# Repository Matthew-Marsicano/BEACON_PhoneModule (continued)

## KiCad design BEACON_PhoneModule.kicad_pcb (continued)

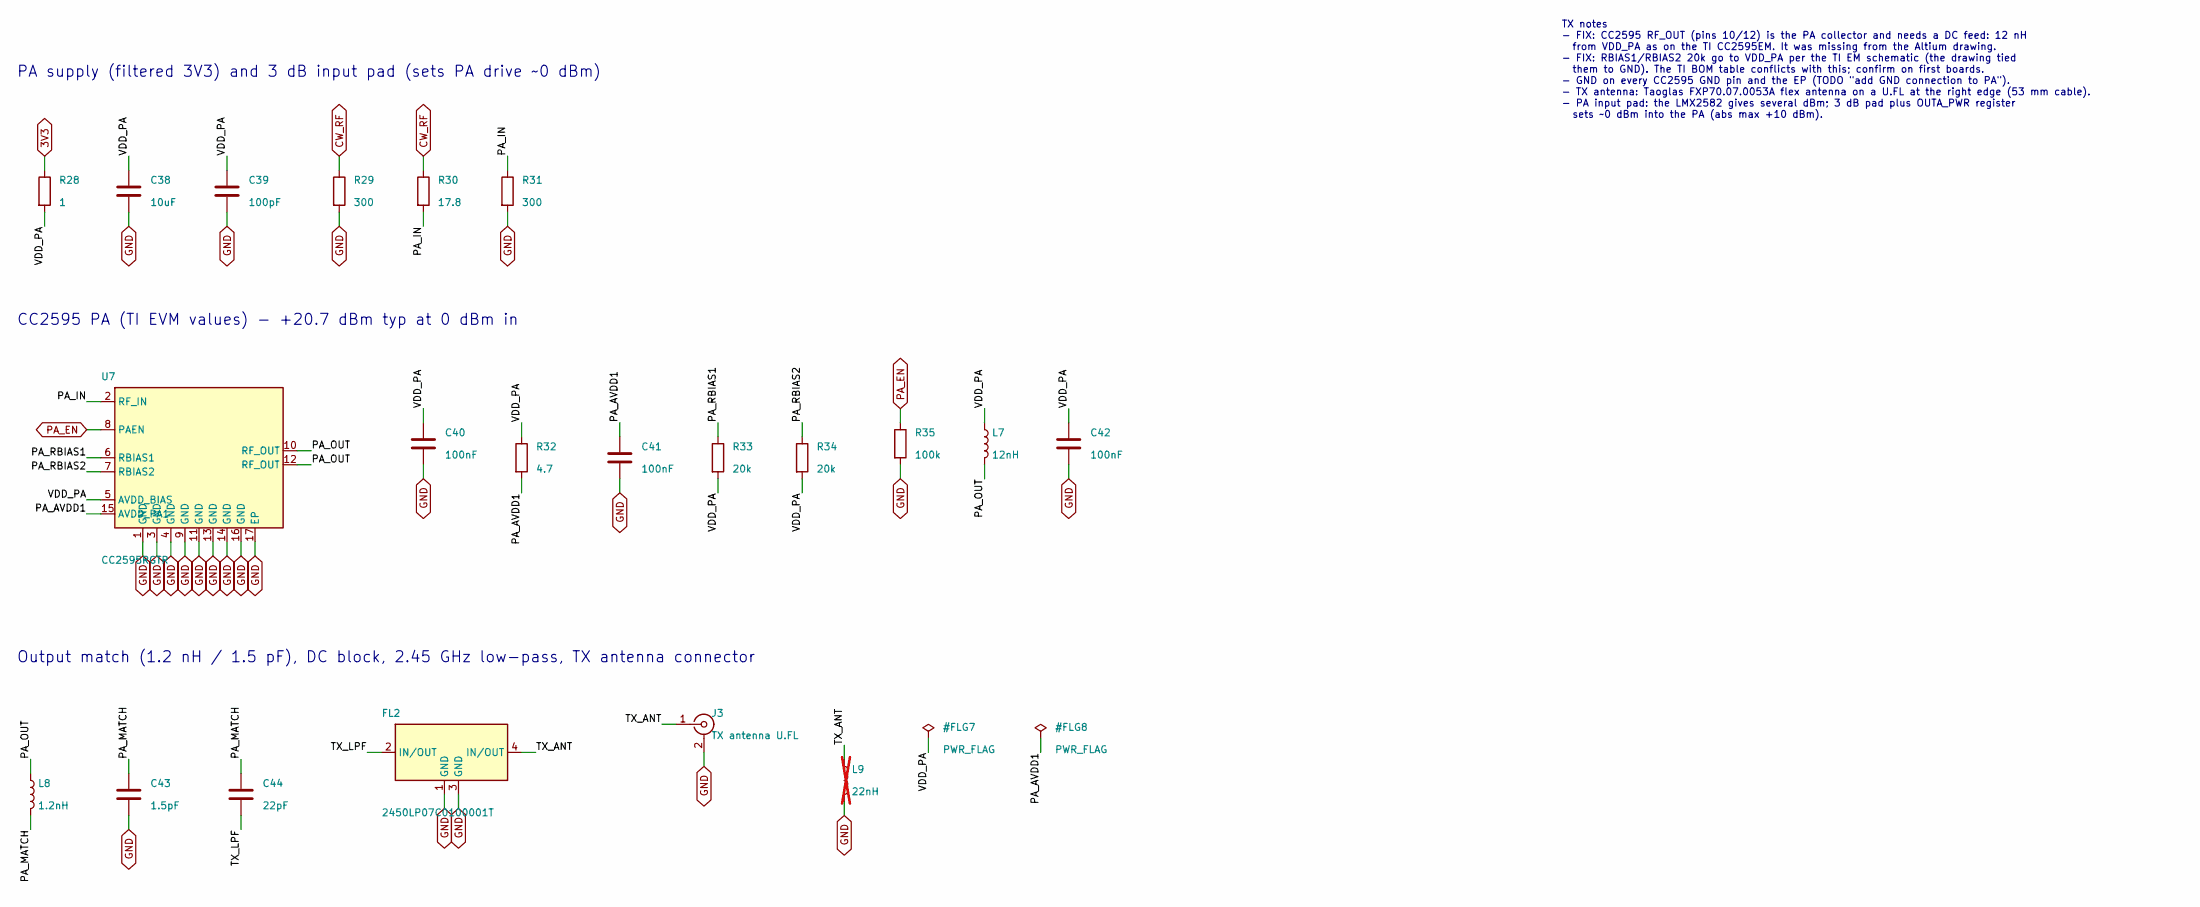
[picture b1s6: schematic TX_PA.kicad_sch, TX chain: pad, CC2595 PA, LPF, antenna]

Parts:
C38: 10uF; C38_C_0603_1608Metric
C39: 100pF; C39_C_0402_1005Metric
C40: 100nF; C40_C_0402_1005Metric
C41: 100nF; C41_C_0402_1005Metric
C42: 100nF; C42_C_0402_1005Metric
C43: 1.5pF; C43_C_0402_1005Metric; MPN 0402CG1R5C500NT
C44: 22pF; C44_C_0402_1005Metric
FL2: 2450LP07C0100001T; FL2_Johanson_2450LP07_0402_4T; MPN 2450LP07C0100001T
J3: TX antenna U.FL; J3_U.FL_Hirose_U.FL-R-SMT-1_Vertical; MPN U.FL-R-SMT-1(10)
L7: 12nH; L7_L_0402_1005Metric; MPN LQW15AN12NG00D; LCSC C86128
L8: 1.2nH; L8_L_0402_1005Metric; MPN LQG15HS1N2B02D; LCSC C488336
L9: 22nH; L9_L_0402_1005Metric; MPN LQW15AN22NJ00D; not fitted
R28: 1; R28_R_0603_1608Metric
R29: 300; R29_R_0402_1005Metric
R30: 17.8; R30_R_0402_1005Metric
R31: 300; R31_R_0402_1005Metric
R32: 4.7; R32_R_0402_1005Metric
R33: 20k; R33_R_0402_1005Metric
R34: 20k; R34_R_0402_1005Metric
R35: 100k; R35_R_0402_1005Metric
U7: CC2595RGTR; U7_VQFN-16-1EP_3x3mm_P0.5mm_EP1.68x1.68mm_ThermalVias; MPN CC2595RGTR

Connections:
3V3: R28.1; also elsewhere on the board
/TX_PA/PA_AVDD1: C41.1, R32.2, U7.15 (AVDD_PA1)
/TX_PA/PA_IN: R30.2, R31.1, U7.2 (RF_IN)
/TX_PA/PA_MATCH: C43.1, C44.1, L8.2
/TX_PA/PA_OUT: L7.2, L8.1, U7.10 (RF_OUT), U7.12 (RF_OUT)
/TX_PA/PA_RBIAS1: R33.1, U7.6 (RBIAS1)
/TX_PA/PA_RBIAS2: R34.1, U7.7 (RBIAS2)
/TX_PA/TX_ANT: FL2.4 (IN/OUT), J3.1 (In), L9.1
/TX_PA/TX_LPF: C44.2, FL2.2 (IN/OUT)
/TX_PA/VDD_PA: C38.1, C39.1, C40.1, C42.1, L7.1, R28.2, R32.1, R33.2, R34.2, U7.5 (AVDD_BIAS)
CW_RF: R29.1, R30.1; also elsewhere on the board
GND: C38.2, C39.2, C40.2, C41.2, C42.2, C43.2, FL2.1 (GND), FL2.3 (GND), J3.2 (Ext), L9.2, R29.2, R31.2, R35.2, U7.1 (GND), U7.3 (GND), U7.4 (GND), U7.9 (GND), U7.11 (GND), U7.13 (GND), U7.14 (GND), U7.16 (GND), U7.17 (EP); also elsewhere on the board
PA_EN: R35.1, U7.8 (PAEN); also elsewhere on the board

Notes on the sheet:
PA supply (filtered 3V3) and 3 dB input pad (sets PA drive ~0 dBm)
CC2595 PA (TI EVM values) - +20.7 dBm typ at 0 dBm in
Output match (1.2 nH / 1.5 pF), DC block, 2.45 GHz low-pass, TX antenna connector
TX notes - FIX: CC2595 RF_OUT (pins 10/12) is the PA collector and needs a DC feed: 12 nH from VDD_PA as on the TI CC2595EM. It was missing from the Altium drawing. - FIX: RBIAS1/RBIAS2 20k go to VDD_PA per the TI EM schematic (the drawing tied them to GND). The TI BOM table conflicts with this; co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

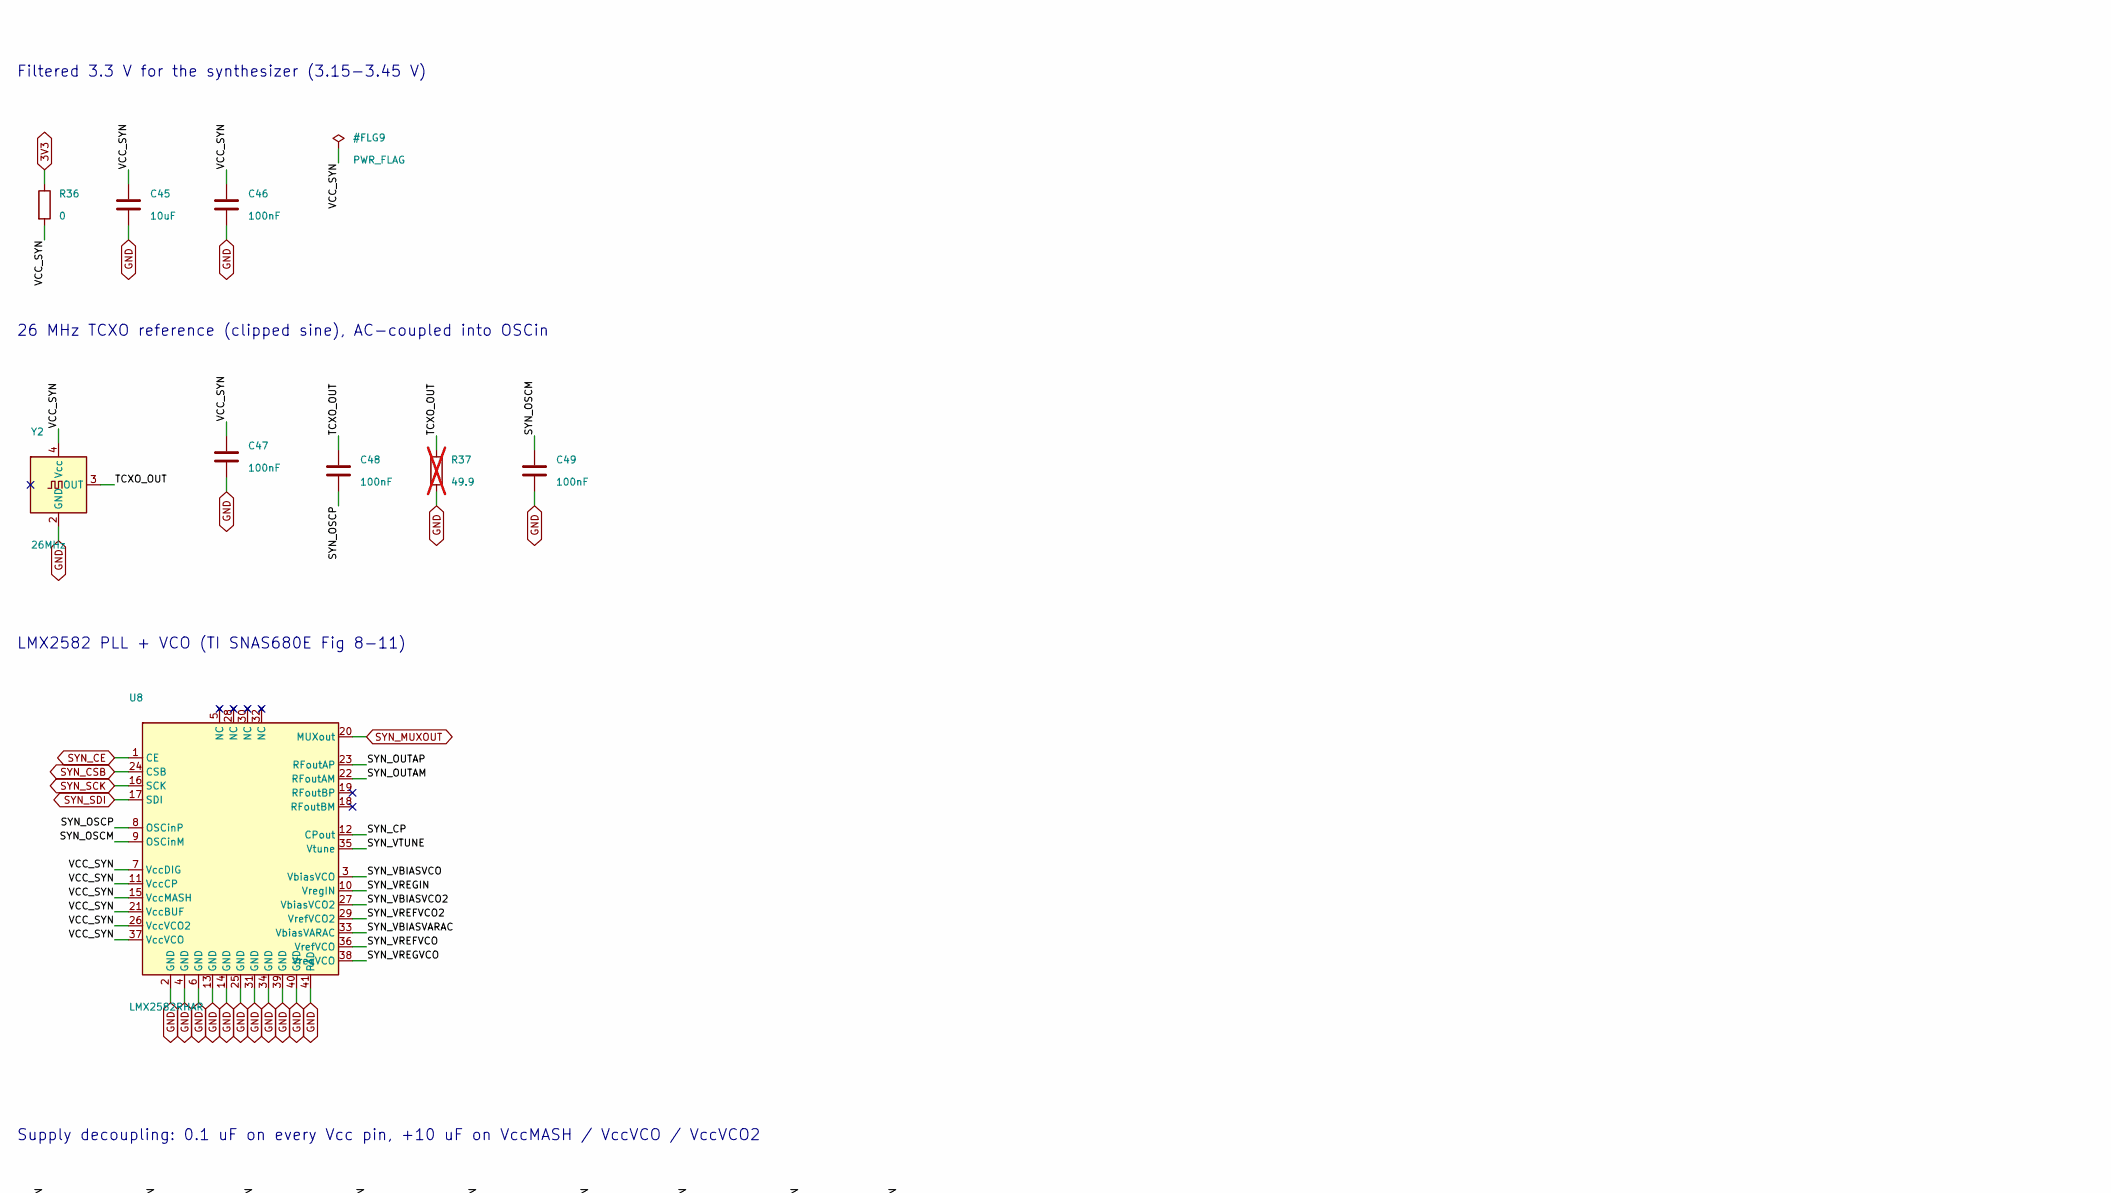
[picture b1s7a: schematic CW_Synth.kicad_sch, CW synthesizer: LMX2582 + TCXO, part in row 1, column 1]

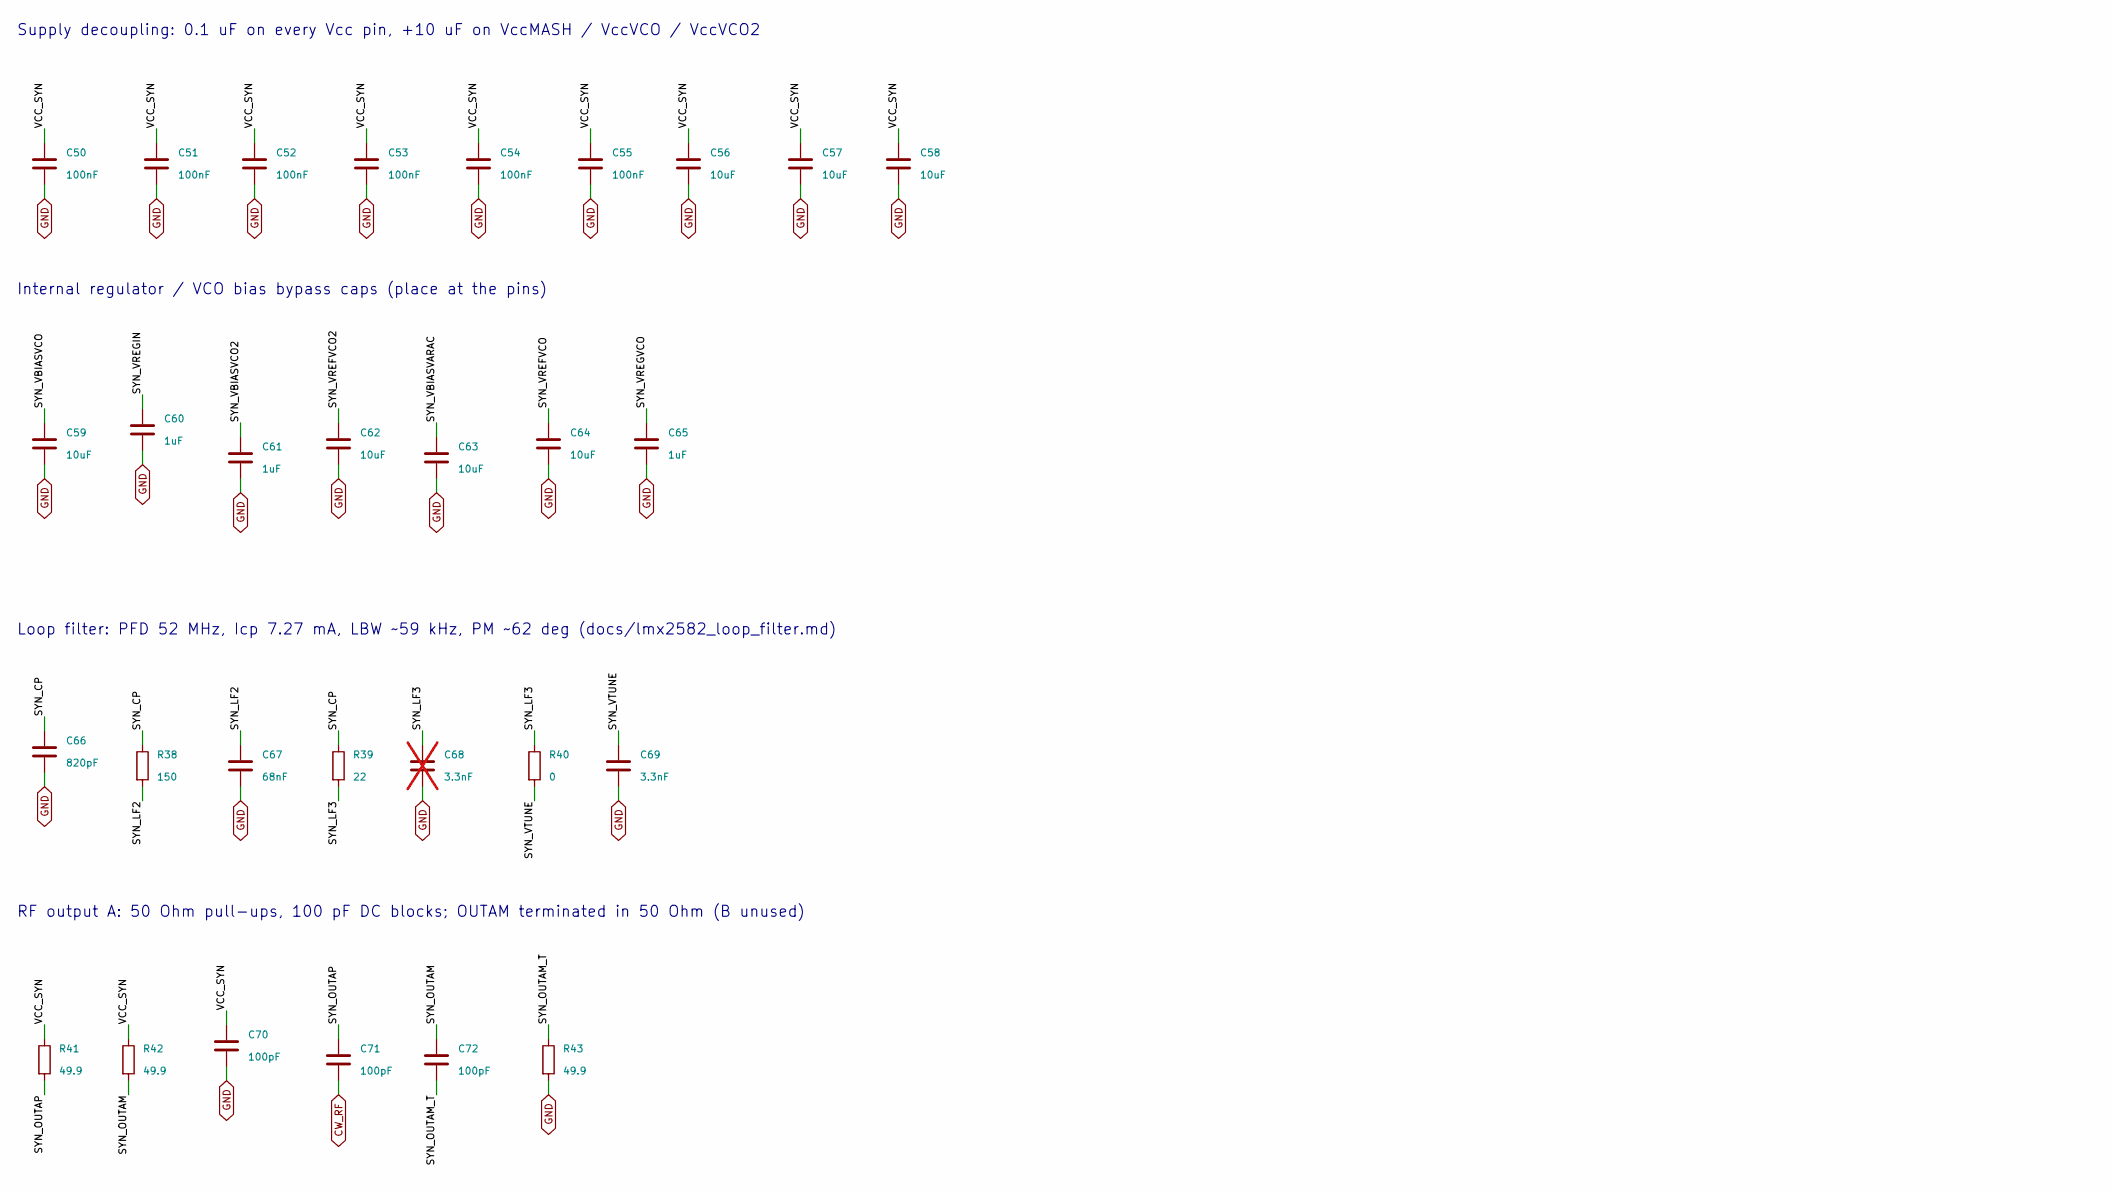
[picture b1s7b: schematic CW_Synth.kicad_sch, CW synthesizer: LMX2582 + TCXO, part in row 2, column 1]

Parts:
C45: 10uF; C45_C_0603_1608Metric
C46: 100nF; C46_C_0402_1005Metric
C47: 100nF; C47_C_0402_1005Metric
C48: 100nF; C48_C_0402_1005Metric
C49: 100nF; C49_C_0402_1005Metric
C50: 100nF; C50_C_0402_1005Metric
C51: 100nF; C51_C_0402_1005Metric
C52: 100nF; C52_C_0402_1005Metric
C53: 100nF; C53_C_0402_1005Metric
C54: 100nF; C54_C_0402_1005Metric
C55: 100nF; C55_C_0402_1005Metric
C56: 10uF; C56_C_0603_1608Metric
C57: 10uF; C57_C_0603_1608Metric
C58: 10uF; C58_C_0603_1608Metric
C59: 10uF; C59_C_0603_1608Metric
C60: 1uF; C60_C_0402_1005Metric
C61: 1uF; C61_C_0402_1005Metric
C62: 10uF; C62_C_0603_1608Metric
C63: 10uF; C63_C_0603_1608Metric
C64: 10uF; C64_C_0603_1608Metric
C65: 1uF; C65_C_0402_1005Metric
C66: 820pF; C66_C_0402_1005Metric
C67: 68nF; C67_C_0603_1608Metric; MPN CL10B683KB8NNNC; LCSC C31658
C68: 3.3nF; C68_C_0402_1005Metric; not fitted
C69: 3.3nF; C69_C_0402_1005Metric
C70: 100pF; C70_C_0402_1005Metric
C71: 100pF; C71_C_0402_1005Metric
C72: 100pF; C72_C_0402_1005Metric
R36: 0; R36_R_0603_1608Metric
R37: 49.9; R37_R_0402_1005Metric; not fitted
R38: 150; R38_R_0402_1005Metric
R39: 22; R39_R_0402_1005Metric
R40: 0; R40_R_0402_1005Metric
R41: 49.9; R41_R_0402_1005Metric
R42: 49.9; R42_R_0402_1005Metric
R43: 49.9; R43_R_0402_1005Metric
U8: LMX2582RHAR; U8_Texas_RHA_VQFN-40-1EP_6x6mm_P0.5mm_EP4.6x4.6mm_ThermalVi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; MPN LMX2582RHAR
Y2: 26MHz; Y2_Oscillator_SMD_SeikoEpson_TG2520SMN-xxx-xxxxxx-4Pin_2.5x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; MPN X1G0054210204; LCSC C7527389

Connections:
3V3: R36.1; also elsewhere on the board
/CW_Synth/SYN_CP: C66.1, R38.1, R39.1, U8.12 (CPout)
/CW_Synth/SYN_LF2: C67.1, R38.2
/CW_Synth/SYN_LF3: C68.1, R39.2, R40.1
/CW_Synth/SYN_OSCM: C49.1, U8.9 (OSCinM)
/CW_Synth/SYN_OSCP: C48.2, U8.8 (OSCinP)
/CW_Synth/SYN_OUTAM: C72.1, R42.2, U8.22 (RFoutAM)
/CW_Synth/SYN_OUTAM_T: C72.2, R43.1
/CW_Synth/SYN_OUTAP: C71.1, R41.2, U8.23 (RFoutAP)
/CW_Synth/SYN_VBIASVARAC: C63.1, U8.33 (VbiasVARAC)
/CW_Synth/SYN_VBIASVCO: C59.1, U8.3 (VbiasVCO)
/CW_Synth/SYN_VBIASVCO2: C61.1, U8.27 (VbiasVCO2)
/CW_Synth/SYN_VREFVCO: C64.1, U8.36 (VrefVCO)
/CW_Synth/SYN_VREFVCO2: C62.1, U8.29 (VrefVCO2)
/CW_Synth/SYN_VREGIN: C60.1, U8.10 (VregIN)
/CW_Synth/SYN_VREGVCO: C65.1, U8.38 (VregVCO)
/CW_Synth/SYN_VTUNE: C69.1, R40.2, U8.35 (Vtune)
/CW_Synth/TCXO_OUT: C48.1, R37.1, Y2.3 (OUT)
/CW_Synth/VCC_SYN: C45.1, C46.1, C47.1, C50.1, C51.1, C52.1, C53.1, C54.1, C55.1, C56.1, C57.1, C58.1, C70.1, R36.2, R41.1, R42.1, U8.7 (VccDIG), U8.11 (VccCP), U8.15 (VccMASH), U8.21 (VccBUF), U8.26 (VccVCO2), U8.37 (VccVCO), Y2.4 (Vcc)
CW_RF: C71.2; also elsewhere on the board
GND: C45.2, C46.2, C47.2, C49.2, C50.2, C51.2, C52.2, C53.2, C54.2, C55.2, C56.2, C57.2, C58.2, C59.2, C60.2, C61.2, C62.2, C63.2, C64.2, C65.2, C66.2, C67.2, C68.2, C69.2, C70.2, R37.2, R43.2, U8.2 (GND), U8.4 (GND), U8.6 (GND), U8.13 (GND), U8.14 (GND), U8.25 (GND), U8.31 (GND), U8.34 (GND), U8.39 (GND), U8.40 (GND), U8.41 (PAD), Y2.2 (GND); also elsewhere on the board
SYN_CE: U8.1 (CE); also elsewhere on the board
SYN_CSB: U8.24 (CSB); also elsewhere on the board
SYN_MUXOUT: U8.20 (MUXout); also elsewhere on the board
SYN_SCK: U8.16 (SCK); also elsewhere on the board
SYN_SDI: U8.17 (SDI); also elsewhere on the board

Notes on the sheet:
Filtered 3.3 V for the synthesizer (3.15-3.45 V)
26 MHz TCXO reference (clipped sine), AC-coupled into OSCin
LMX2582 PLL + VCO (TI SNAS680E Fig 8-11)
Supply decoupling: 0.1 uF on every Vcc pin, +10 uF on VccMASH / VccVCO / VccVCO2
Internal regulator / VCO bias bypass caps (place at the pins)
Loop filter: PFD 52 MHz, Icp 7.27 mA, LBW ~59 kHz, PM ~62 deg (docs/lmx2582_loop_filter.md)
RF output A: 50 Ohm pull-ups, 100 pF DC blocks; OUTAM terminated in 50 Ohm (B unused)
CW synthesizer notes (completed from the TI typical application) - Carrier: 2400-2483.5 MHz ISM. VCO 3.55-7.1 GHz, CHDIV=2 -> 2.4 GHz on OUTA. - Reference: 26 MHz TCXO. The PFD can use the OSCin doubler (52 MHz) in fractional mode. - SPI: SCK/SDI/CSB from the nRF52840; MUXout = lock detect or SPI r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

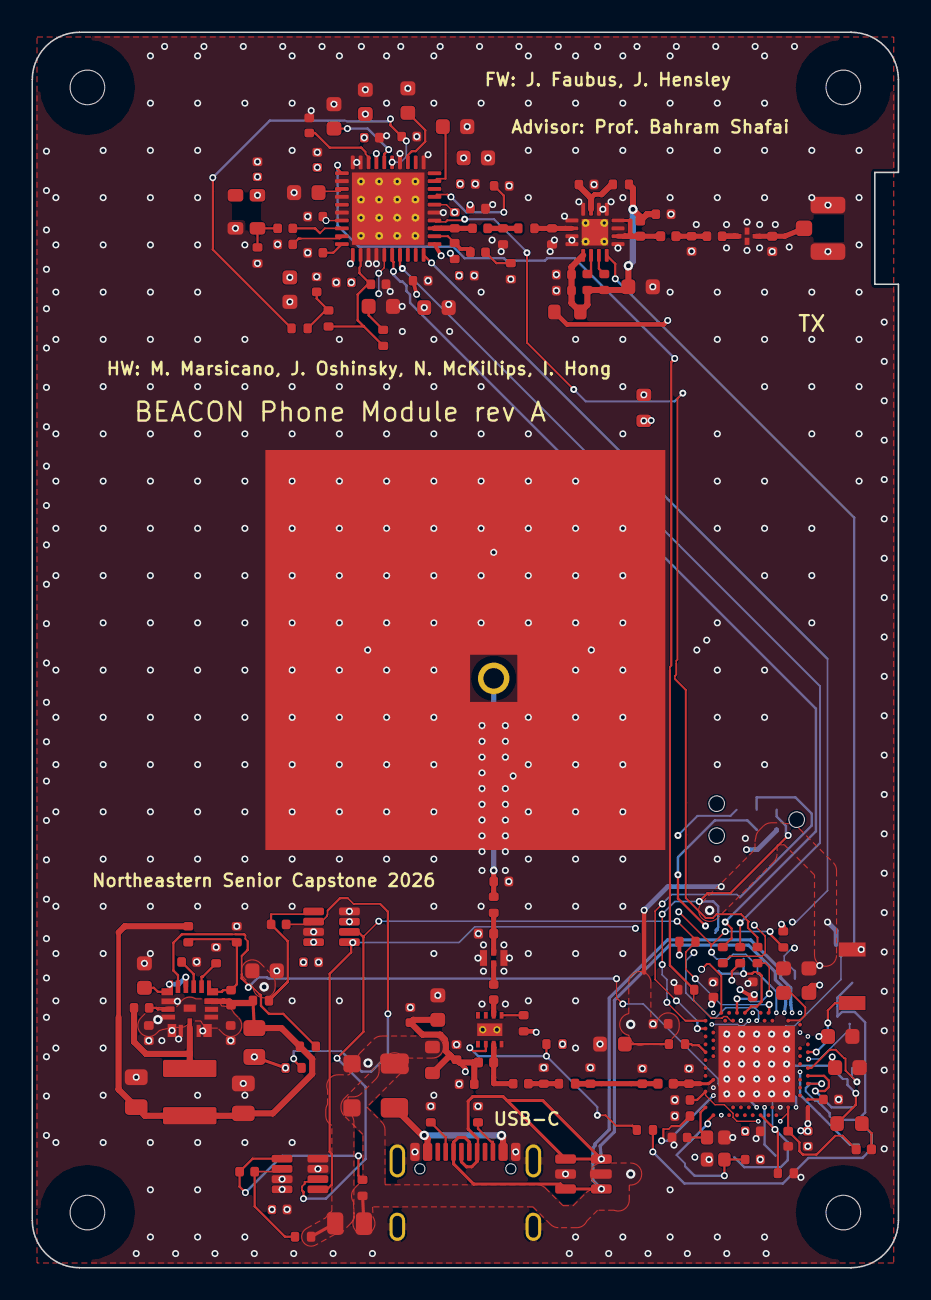
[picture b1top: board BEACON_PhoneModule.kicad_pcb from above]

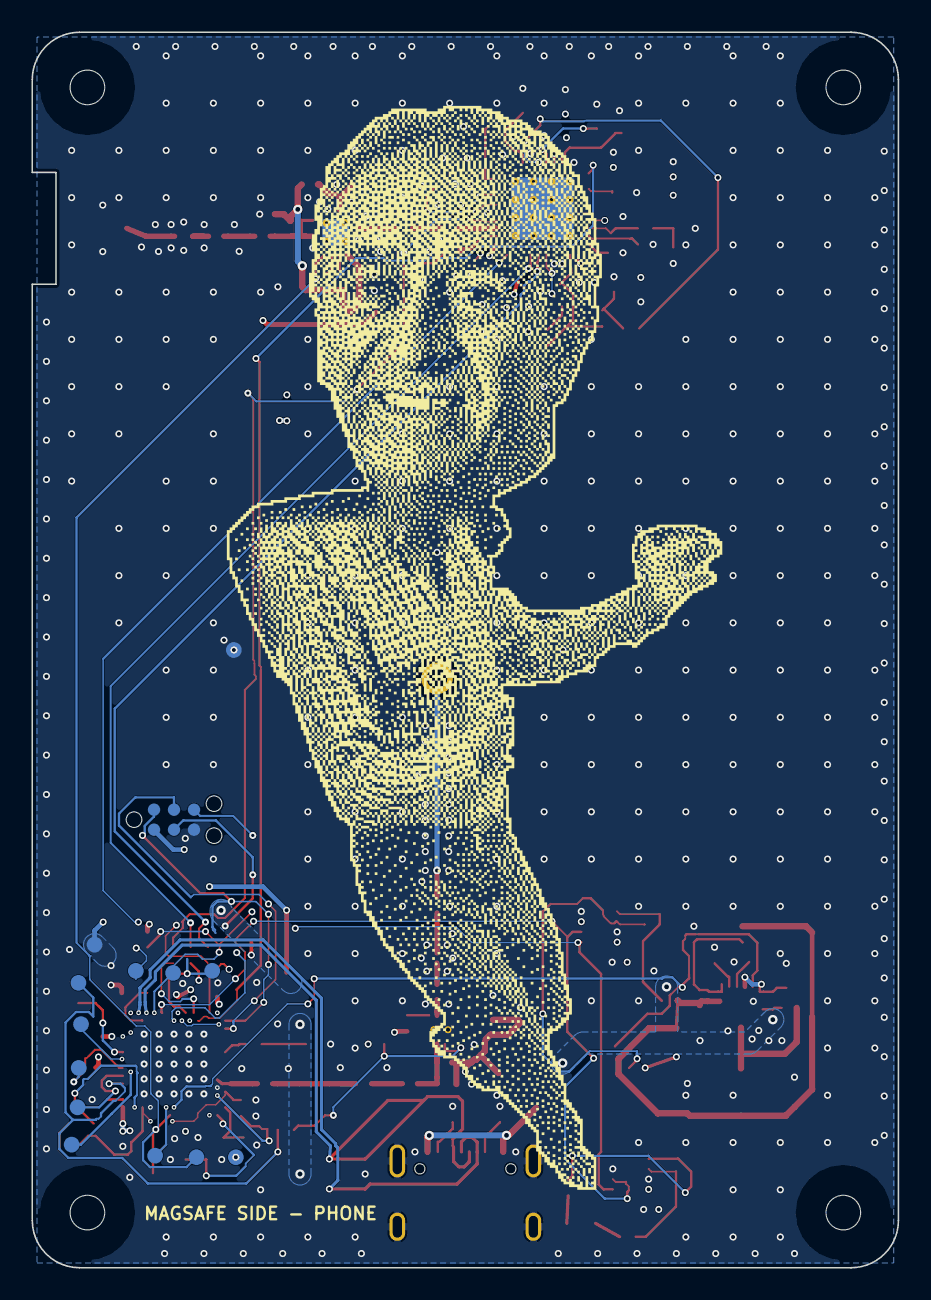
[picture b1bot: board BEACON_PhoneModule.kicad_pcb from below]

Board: 4 copper layers, 55.0 x 78.4 mm, 161 parts (14 on the bottom side), 92 nets.

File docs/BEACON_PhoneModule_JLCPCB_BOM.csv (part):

Comment,Designator,Footprint,LCSC Part #,MPN,Manufacturer,Quantity,Type,Notes
1uF,"C1,C16,C25,C35,C60,C61,C65",C_0402_1005Metric,C52923,CL05A105KA5NQNC,Samsung Electro-Mechanics,7,Basic,"1uF 25V X5R 10%. 25 V covers the 5V_BUS/5V0/LNA_VCC caps (C1, C35)."
100nF,"C2,C3,C4,C5,C7,C8,C11,C17,C18,C19,C23,C40,C41,C42,C46,C47,C48,C49,C50,C51,C52,C53,C54,C55",C_0402_1005Metric,C1525,CL05B104KO5NNNC,Samsung Electro-Mechanics,24,Basic,"100nF 16V X7R 10%. 16 V covers the 5V0 hot-loop caps (C7, C8)."
4.7uF,"C6,C15,C20,C21,C22",C_0603_1608Metric,C19666,CL10A475KO8NNNC,Samsung Electro-Mechanics,5,Basic,4.7uF 16V X5R 10%. 16 V covers 5V0 (C6) and VBUS (C21).
22nF,C9,C_0402_1005Metric,C1532,0402B223K500NT,FH,1,Basic,"SWAP (2026-11-02): was 18nF GCM155R71H183KA55D (C710669, extended). 22nF 50V X7R 10% Basic part. Soft-start ramp about 22% slower, still milliseconds."
2.2uF,C10,C_0603_1608Metric,C23630,CL10A225KO8NNNC,Samsung Electro-Mechanics,1,Basic,2.2uF 16V X5R (INTVCC).
4.7pF,C12,C_0402_1005Metric,C1569,0402CG4R7C500NT,FH,1,Extended (Preferred),4.7pF 50V C0G +/-0.25pF (FB feed-forward). Preferred-extended part.
22uF,"C13,C14",C_0805_2012Metric,C45783,CL21A226MAQNNNE,Samsung Electro-Mechanics,2,Basic,22uF 25V X5R 20% 0805.
100pF,"C24,C32,C33,C36,C37,C39,C70,C71,C72",C_0402_1005Metric,C1546,0402CG101J500NT,FH,9,Basic,100pF 50V C0G 5% (RF DC blocks and decoupling).
47nF,C26,C_0402_1005Metric,C272875,CC0402KRX7R9BB473,YAGEO,1,Extended,47nF 50V X7R 10% (nRF DEC4/6). No Basic 47 nF 0402 exists.
12pF,"C27,C28",C_0402_1005Metric,C1547,0402CG120J500NT,FH,2,Basic,12pF 50V C0G 5% (32 MHz crystal load caps).
0.8pF,C29,C_0402_1005Metric,C76915,GJM1555C1HR80BB01D,muRata,1,Extended,"Exact MPN, Murata GJM high-Q C0G 0.8pF +/-0.1pF (nRF ANT match)."
0.5pF,C30,C_0402_1005Metric,C76911,GJM1555C1HR50BB01D,muRata,1,Extended,"Exact MPN, Murata GJM high-Q C0G 0.5pF +/-0.1pF (nRF ANT match)."
10uF,"C34,C38,C45,C56,C57,C58,C59,C62,C63,C64",C_0603_1608Metric,C96446,CL10A106MA8NRNC,Samsung Electro-Mechanics,10,Basic,"10uF 25V X5R 20%. 25 V covers LNA_VCC (C34, about 4.35 V). C19702 (10 V) also works for the 3V3-only caps."
1.5pF,C43,C_0402_1005Metric,C1552,0402CG1R5C500NT,FH,1,Extended (Preferred),"SWAP (2026-11-02): was Murata GJM1555C1H1R5BB01D (C76900, high-Q). FH 1.5pF 50V C0G +/-0.25pF preferred-extended part, slightly lower Q (PA output match)."
22pF,C44,C_0402_1005Metric,C1555,0402CG220J500NT,FH,1,Basic,22pF 50V C0G 5% (PA DC block).
820pF,C66,C_0402_1005Metric,C296004,0402N821J500CT,Walsin,1,Extended,820pF 50V NP0/C0G 5% (loop-filter C1). If it runs short: C161159 GCM1555C1H821JA16D (Murata C0G).
68nF,C67,C_0603_1608Metric,C31658,CL10B683KB8NNNC,Samsung Electro-Mechanics,1,Extended (Preferred),"APPROVED SUB (user, 2026-11-02). FLAG: no 68nF C0G in 0603 is stocked at LCSC. This is X7R 50V 10% (preferred-extended). The 50 V rating keeps DC-bias loss small at the <3.3 V Vtune node. A C0G part would need an 0805/1206 footprint."
3.3nF,C69,C_0402_1005Metric,C1518207,GRM1555C1H332JE01D,muRata,1,Extended,3.3nF 50V C0G 5% (loop-filter C4 at Vtune).
SZSMF6.0AT1G,D1,D_SOD-123F,C1975319,SZSMF6.0AT1G,Littelfuse (ex-onsemi),1,Extended,"Exact MPN. LCSC stock is low (20), so reserve or order now."
Red,D2,LED_0603_1608Metric,C2286,KT-0603R,Hubei KENTO,1,Basic,"Exact MPN. KT-0603R is a Hubei KENTO part, not Kingbright, so the schematic Manufacturer field is wrong. JLC Basic part."
0.75A hold,F1,Fuse_1206_3216Metric,C315953,NANOSMDC075F-2,Littelfuse,1,Extended,Exact MPN (LCSC lists it as NANOSMDC075F-2/RF1348-000).
DEA202450BT-1294D1-H,FL1,TDK_DEA202450BT-1294D1-H_2012,C1512913,DEA202450BT-1294D1-H,TDK,1,Extended,"APPROVED SUB (user, 2026-11-02): replaces Johanson 2450BP08C0100001T (no stock anywhere). IL 1.02 typ / 1.35 max dB, 1 W. See docs/bpf_alternative.md"
2450LP07C0100001T,FL2,Johanson_2450LP07_0402_4T,C17630068,2450LP07C0100001T,Johanson Dielectrics,1,Extended,"FLAG: exact MPN is listed at LCSC but stock is 0 (""Pre/New""). Pre-order it into your JLC parts inventory, or consign it (DigiKey/Mouser) or hand-solder."
USB4105-GF-A,J1,USB_C_Receptacle_GCT_USB4105-xx-A_16P_TopMnt_Horizontal,C3020560,USB4105-GF-A,Global Connector Technology,1,Extended,Exact MPN. LCSC stock 465.
TX antenna U.FL,J3,U.FL_Hirose_U.FL-R-SMT-1_Vertical,C88374,U.FL-R-SMT-1(10),Hirose,1,Extended,"Hirose U.FL-R-SMT-1(80), C88374, JLC stock 360,956. It is the same connector as the U.FL-R-SMT-1(10) in the schematic, on a different reel. The exact (10) part, C88373, has only 65 pcs (pre-order)."
5.6uH,L1,L_Abracon_ASPI-4030S,C5224561,ASPI-4030S-5R6M-T,Abracon,1,Extended,"APPROVED SUB (user, 2026-11-02): replaces Wurth 74438357056; Isat 2.6 A vs ~0.56 A peak; footprint changed to L_Abracon_ASPI-4030S (pads 1.1 x 3.4 at +-1.5 mm)"
4.7nH,L4,L_0402_1005Metric,C162543,LQG15HS4N7B02D,Murata,1,Extended,"APPROVED SUB (user, 2026-11-02). FLAG ALT: exact LQP15MN4N7B02D (C23769) has 0 stock. LQG15HS4N7B02D is the same 0402 size, 4.7nH +/-0.1nH, 700 mA (multilayer, slightly lower Q). Thin-film alternative: C1330427 ABRACON ATFC-0402-4N7B-T."
18nH,L6,L_0402_1005Metric,C22398296,0402CS-18NXGRW,Coilcraft,1,Extended,"Exact MPN (Coilcraft). LCSC stock is low (49), so order now."
12nH,L7,L_0402_1005Metric,C86128,LQW15AN12NG00D,Murata,1,Extended,"APPROVED SUB (user, 2026-11-02). FLAG ALT: exact LQW15AN12NJ00D (C82920) has 0 stock. LQW15AN12NG00D is identical except for tolerance (+/-2% vs +/-5%): same series, 500 mA, 140 mOhm, non-magnetic."
1.2nH,L8,L_0402_1005Metric,C488336,LQG15HS1N2B02D,Murata,1,Extended,"APPROVED SUB (user, 2026-11-02). FLAG ALT: exact LQP15MN1N2B02D (C77117) has 0 stock and is reported obsolete. LQG15HS1N2B02D is 0402, 1.2nH +/-0.1nH, 1 A, 70 mOhm (multilayer)."
5.1k,"R1,R2",R_0402_1005Metric,C25905,0402WGF5101TCE,UNI-ROYAL,2,Basic,5.1k 1% (CC pull-downs).
50m,"R3,R6",R_0805_2012Metric,C2075868,ERJ-6BWFR050V,PANASONIC,2,Extended,"Exact MPN, 50 mOhm 1% 0.5 W 0805 shunt. LCSC 17,450 stock. Fallback: C858632 YAGEO PE0805FRM470R05L."
10,"R4,R5,R7,R8",R_0402_1005Metric,C25077,0402WGF100JTCE,UNI-ROYAL,4,Basic,10R 1%.
37.4k,R9,R_0402_1005Metric,C25888,0402WGF3742TCE,UNI-ROYAL,1,Extended,37.4k 1% (buck RT). No Basic part exists for this value.
634k,R10,R_0402_1005Metric,C270588,0402WGF6343TCE,UNI-ROYAL,1,Extended,634k 1% (buck FB top). No Basic part exists.
200k,R11,R_0402_1005Metric,C25764,0402WGF2003TCE,UNI-ROYAL,1,Basic,200k 1% (buck FB bottom).
10k,R12,R_0402_1005Metric,C25744,0402WGF1002TCE,UNI-ROYAL,1,Basic,10k 1%.
4.7k,"R13,R14",R_0402_1005Metric,C25900,0402WGF4701TCE,UNI-ROYAL,2,Basic,4.7k 1% (I2C pull-ups).
100k,"R15,R27,R35",R_0402_1005Metric,C25741,0402WGF1003TCE,UNI-ROYAL,3,Basic,100k 1%.
33,"R16,R17,R18",R_0402_1005Metric,C25105,0402WGF330JTCE,UNI-ROYAL,3,Basic,33R 1%.
1.5k,R19,R_0402_1005Metric,C25867,0402WGF1501TCE,UNI-ROYAL,1,Basic,1.5k 1%.
0,"R20,R21,R26,R40",R_0402_1005Metric,C17168,0402WGF0000TCE,UNI-ROYAL,4,Basic,0R jumper 0402.
3.3k,R24,R_0402_1005Metric,C25890,0402WGF3301TCE,UNI-ROYAL,1,Basic,"SWAP (2026-11-02): was 3.32k RC0402FR-073K32L (C137993, extended). 3.3k 1% Basic part, LNA bias current changes 0.6%."
10,R25,R_0603_1608Metric,C22859,0603WAF100JT5E,UNI-ROYAL,1,Basic,10R 1% 0603 (LNA RC filter).
1,R28,R_0603_1608Metric,C22936,0603WAF100KT5E,UNI-ROYAL,1,Basic,1R 1% 0603 (PA RC filter).
300,"R29,R31",R_0402_1005Metric,C25102,0402WGF3000TCE,UNI-ROYAL,2,Extended (Preferred),"SWAP (2026-11-02): was 294R 0402WGF2940TCE (C270618, extended). 300R 1% preferred-extended part. The pi pad with R30 17.8R is still 3.02 dB, S11 -47 dB."
17.8,R30,R_0402_1005Metric,C245886,RC0402FR-0717R8L,YAGEO,1,Extended,17.8R 1% (PA input pad). No Basic part exists. Fallback: C2077103 Panasonic ERJ2RKF17R8X.
4.7,R32,R_0402_1005Metric,C25121,0402WGF470KTCE,UNI-ROYAL,1,Extended,4.7R 1%. No Basic part exists.
20k,"R33,R34",R_0402_1005Metric,C25765,0402WGF2002TCE,UNI-ROYAL,2,Basic,20k 1% (CC2595 RBIAS).
0,R36,R_0603_1608Metric,C21189,0603WAF0000T5E,UNI-ROYAL,1,Basic,0R jumper 0603 (synth supply link).
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
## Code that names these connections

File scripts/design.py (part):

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         '  so the DC/DC inductors are DNP footprints. VBUS from USB for the USBD peripheral.\n'
         '- Removed wearable-only nets copied from the wearable MCU sheet: CTRL_SPDT, Mod_Sel0/1,\n'
         '  PMIC_Status0-2, Sensor_SDA/SCL/INT/EN, QSPI_CLK.\n'
         '- GPIO map: SYN_SCK P0.19, SYN_MUXOUT P0.20, SYN_SDI P0.21, SYN_CSB P0.22, SYN_CE P0.23,\n'
         '  I2C SCL P0.13 / SDA P0.15, PA_EN P0.02, LNA_PD P0.26, 3V3_PG P0.03, LED P1.06,\n'
         '  BUTTON P1.09, UART TX P0.06 / RX P0.08, spares P0.28 / P0.04 / P0.05, SWO P1.00.\n'
         '- P0.02, P0.03, P0.28 and P1.06 are radio-sensitive (<=10 kHz, standard drive):\n'
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R(cw, '22', 'SYN_CP', 'SYN_LF3', props={'Note': 'R3_LF (3rd pole)'})
C(cw, '3.3nF', 'SYN_LF3', dnp=True, props={'Note': 'C3_LF - DNP (footprint kept)'})
R(cw, '0', 'SYN_LF3', 'SYN_VTUNE', props={'Note': 'R4_LF (4th pole)'})
C(cw, '3.3nF', 'SYN_VTUNE', props={'Note': 'C4_LF C0G at Vtune pin 35 (>= 3.3 nF required)'})
cw.group('RF output A: 50 Ohm pull-ups, 100 pF DC blocks; OUTAM terminated in 50 Ohm (B unused)')
R(cw, '49.9', 'VCC_SYN', 'SYN_OUTAP', props={'Note': 'Pull-up at pin'})
R(cw, '49.9', 'VCC_SYN', 'SYN_OUTAM', props={'Note': 'Pull-up at pin'})
C(cw, '100pF', 'VCC_SYN', props={'Note': 'Pull-up common node'})
C(cw, '100pF', 'SYN_OUTAP', 'CW_RF', props={'Note': 'DC block -> PA'})
C(cw, '100pF', 'SYN_OUTAM', 'SYN_OUTAM_T', props={'Note': 'DC block'})
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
